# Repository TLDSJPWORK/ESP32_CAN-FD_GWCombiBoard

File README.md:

# ESP32 CAN-FD GateWay CombiBoard

ESP32開発ボード と MCP2518 + MCP2562FD CAN FD Busモジュール x2 を接続するための実験用基板、ESP32_CAN-FD_GWCombiBoardの資料です。

## 特徴

- [ESP32-DevKitC-32E](https://akizukidenshi.com/catalog/g/g115673/)、[ESP32-DevKitC-VE](https://akizukidenshi.com/catalog/g/g115674/)、[AE-ESP32-WROOM-32E-MINI](https://akizukidenshi.com/catalog/g/g116108/)に、[CAN FDモジュール](https://github.com/TLDSJPWORK/CAN-FD_Board)、[有機ELディスプレイ（SSD1306）](https://akizukidenshi.com/catalog/g/g112031/)、[三端子DC/DCレギュレーター](https://akizukidenshi.com/catalog/g/g111188/)をまとめて接続できる実験用基板です。モジュール間の配線の手間を減らし、通信実験の環境を組み立てやすくします。
- CAN FDモジュールを2個接続できるため、1台のESP32で2系統のCANバスを扱う構成を作れます。2つのバス間でメッセージを転送するゲートウェイの実験にも使えます。
- MCP2518向けのドライバ・ライブラリを使い、CANおよびCAN FDの送受信をプログラムできます。各チャンネルのGPIO割当は[仕様書](docs/hardware.md)にまとめています。
- 2系統のCAN信号と外部電源をDB9（D-Sub）コネクタにまとめられるため、実験装置への接続をケーブルで整理できます。
- [有機ELディスプレイ（SSD1306）](https://akizukidenshi.com/catalog/g/g112031/)用のMonitor端子を備え、通信状態や受信データを表示する構成に拡張できます。
- 三端子DC/DCレギュレーターを取り付けることで、12V電源から5Vへ降圧して給電する構成を作れます。
- KiCad設計データ・基板STEP・上下筐体STLを公開しているため、配線の確認や独自の改造、筐体の製作にも活用できます。

[双方向Gatewayサンプル](example/PassThroughGateway/README.md)を収録しています。通常CAN（500 kbit/s）とCAN FD（公称500 kbit/s、BRS時データ2 Mbit/s）の双方向転送を確認しています。試験条件と確認範囲はサンプルの説明を参照してください。

## 基板

DB9のみ実装した販売状態の実物写真です。その他の部品は未実装です。

| 表面 | 裏面 |
|---|---|
|  |  |

## 基板の設定

DB9は実装済みです。ESP32、CANモジュール、表示器、DC/DCなどは用途に応じて別途実装をお願い致します。

| 接続部 | 使い方 |
|---|---|
| J1・J2・J5 | ESP32開発ボードを接続します。3V3・5V・GNDと端子番号を合わせて取り付けます。 |
| J9・J10 | CAN FDモジュールの8ピン端子を接続します。モジュールの動作電圧ジャンパは3.3Vに設定して下さい |
| J3（Ch1）・J4（Ch2） | 各CANモジュールのCAN側端子を接続します。1番=CAN-H、2番=CAN-L、3番=GNDです。 |
| J6（Monitor） | SSD1306表示器用。1番=GND、2番=5V、3番=GPIO22、4番=GPIO21です。表示器側の端子順も確認してください。 |
| J7 | BP5293-50を接続します。1番=12V入力、2番=GND、3番=5V出力です。 |
| J8 | 外部電源入力。1番=12V、2番=GNDです。 |
| DB1（DB9・実装済み） | 販売時に実装済みです。2系統のCAN信号と外部電源をまとめて接続します。配列は[仕様書](docs/hardware.md)を参照してください。 |

CANの終端抵抗はCANモジュール側で設定し、各バスの両端で有効にします。外部電源とUSB給電は併用しない前提です。詳しい実装手順は[組立ガイド](docs/assembly.md)を参照してください。

## 対応部品・設計仕様

- 対応ESP32開発ボード：ESP32-DevKitC-32E／ESP32-DevKitC-VE／AE-ESP32-WROOM-32E-MINIのいずれか×1
- MCP2518 + MCP2562FD CAN FD Busモジュール（JP-WORKS-002）×1〜2
- 外部給電用DC/DC：BP5293-50（部品定格：入力7〜26V、出力5V・最大1A）
- 設計外形94×85mm、厚さ1.6mm
- DB9に2系統CANと外部電源を配置。端子配列は[仕様書](docs/hardware.md)を確認してください。

外部電源とUSB給電は併用しない前提です。部品定格は組立例全体の動作保証範囲ではありません。

## 内容物・別途必要な部品

販売内容物はDB9コネクタ実装済みの基板1枚です。その他の部品は別途購入し、はんだ付けして実装する構成です。
必要な部品と取付方法は[組立ガイド](docs/assembly.md)を参照してください。

## 使用例

ESP32開発ボードとCAN FDモジュール2枚を取り付け、DB9ケーブルを接続した組立例です。Monitor端子から表示器へ配線し、3Dプリントした上下筐体に収めています。本例ではUSB給電を前提としたため、筐体を一部切断し、USBをESP32に挿せるようにしております。

| モジュールを取り付けた状態 | 筐体に収めた状態 |
|---|---|
|  |  |

写真のESP32、CAN FDモジュール、表示器、ケーブル、筐体は販売品に含まれません。部品の向きは[組立ガイド](docs/assembly.md)、筐体データは[こちら](mechanical/README.md)を参照してください。

- [GateWay CombiBoardの組立と2バス通信の紹介（note）](https://note.com/tldsjpwork/n/n04cee544bb15)

## 資料

- [仕様・接続表](docs/hardware.md)
- [組立・動作確認ガイド](docs/assembly.md)
- [KiCad設計データ](hardware/kicad/)
- [製造データ](hardware/production/)
- [筐体・3Dデータ](mechanical/)
- [上下筐体のSTL・印刷ガイド（MakerWorld）](https://makerworld.com/ja/models/3444573-upper-and-lower-enclosure-for-esp32-can-fd-gateway)
- [ソフトウェアについて](example/README.md)
- [収録データとライセンス](docs/publication.md)

[回路図PDF](docs/schematic.pdf)も用意しております。基板の表裏写真、接続説明図、組立例を上記に掲載しています。

## 販売・問い合わせ

スイッチサイエンス様にて委託販売中
- [GateWay CombiBoardの販売ページ](https://www.switch-science.com/products/11498)
- 技術問い合わせ先：tldsjpwork@gmail.com

## ライセンス

本プロジェクトのオリジナル設計・製造データ・筐体データ・資料は[CC BY 4.0](LICENSE)で公開します。出典表示：JP WORKS / TLDSJPWORK、ESP32 CAN-FD GateWay CombiBoard。変更した場合は変更内容を明示してください。第三者の素材・ライブラリはそれぞれの利用条件に従います。

## 関連プロジェクト

- [CAN-FD_Board](https://github.com/TLDSJPWORK/CAN-FD_Board)：本基板に接続するCAN FD対応モジュールです。1チャンネルにつき1枚使用します。
- [ESP32_CAN-FD_CombiBoard](https://github.com/TLDSJPWORK/ESP32_CAN-FD_CombiBoard)：CANが1チャンネルでよい用途向けの接続基板です。用途に応じてこちらもご検討ください。

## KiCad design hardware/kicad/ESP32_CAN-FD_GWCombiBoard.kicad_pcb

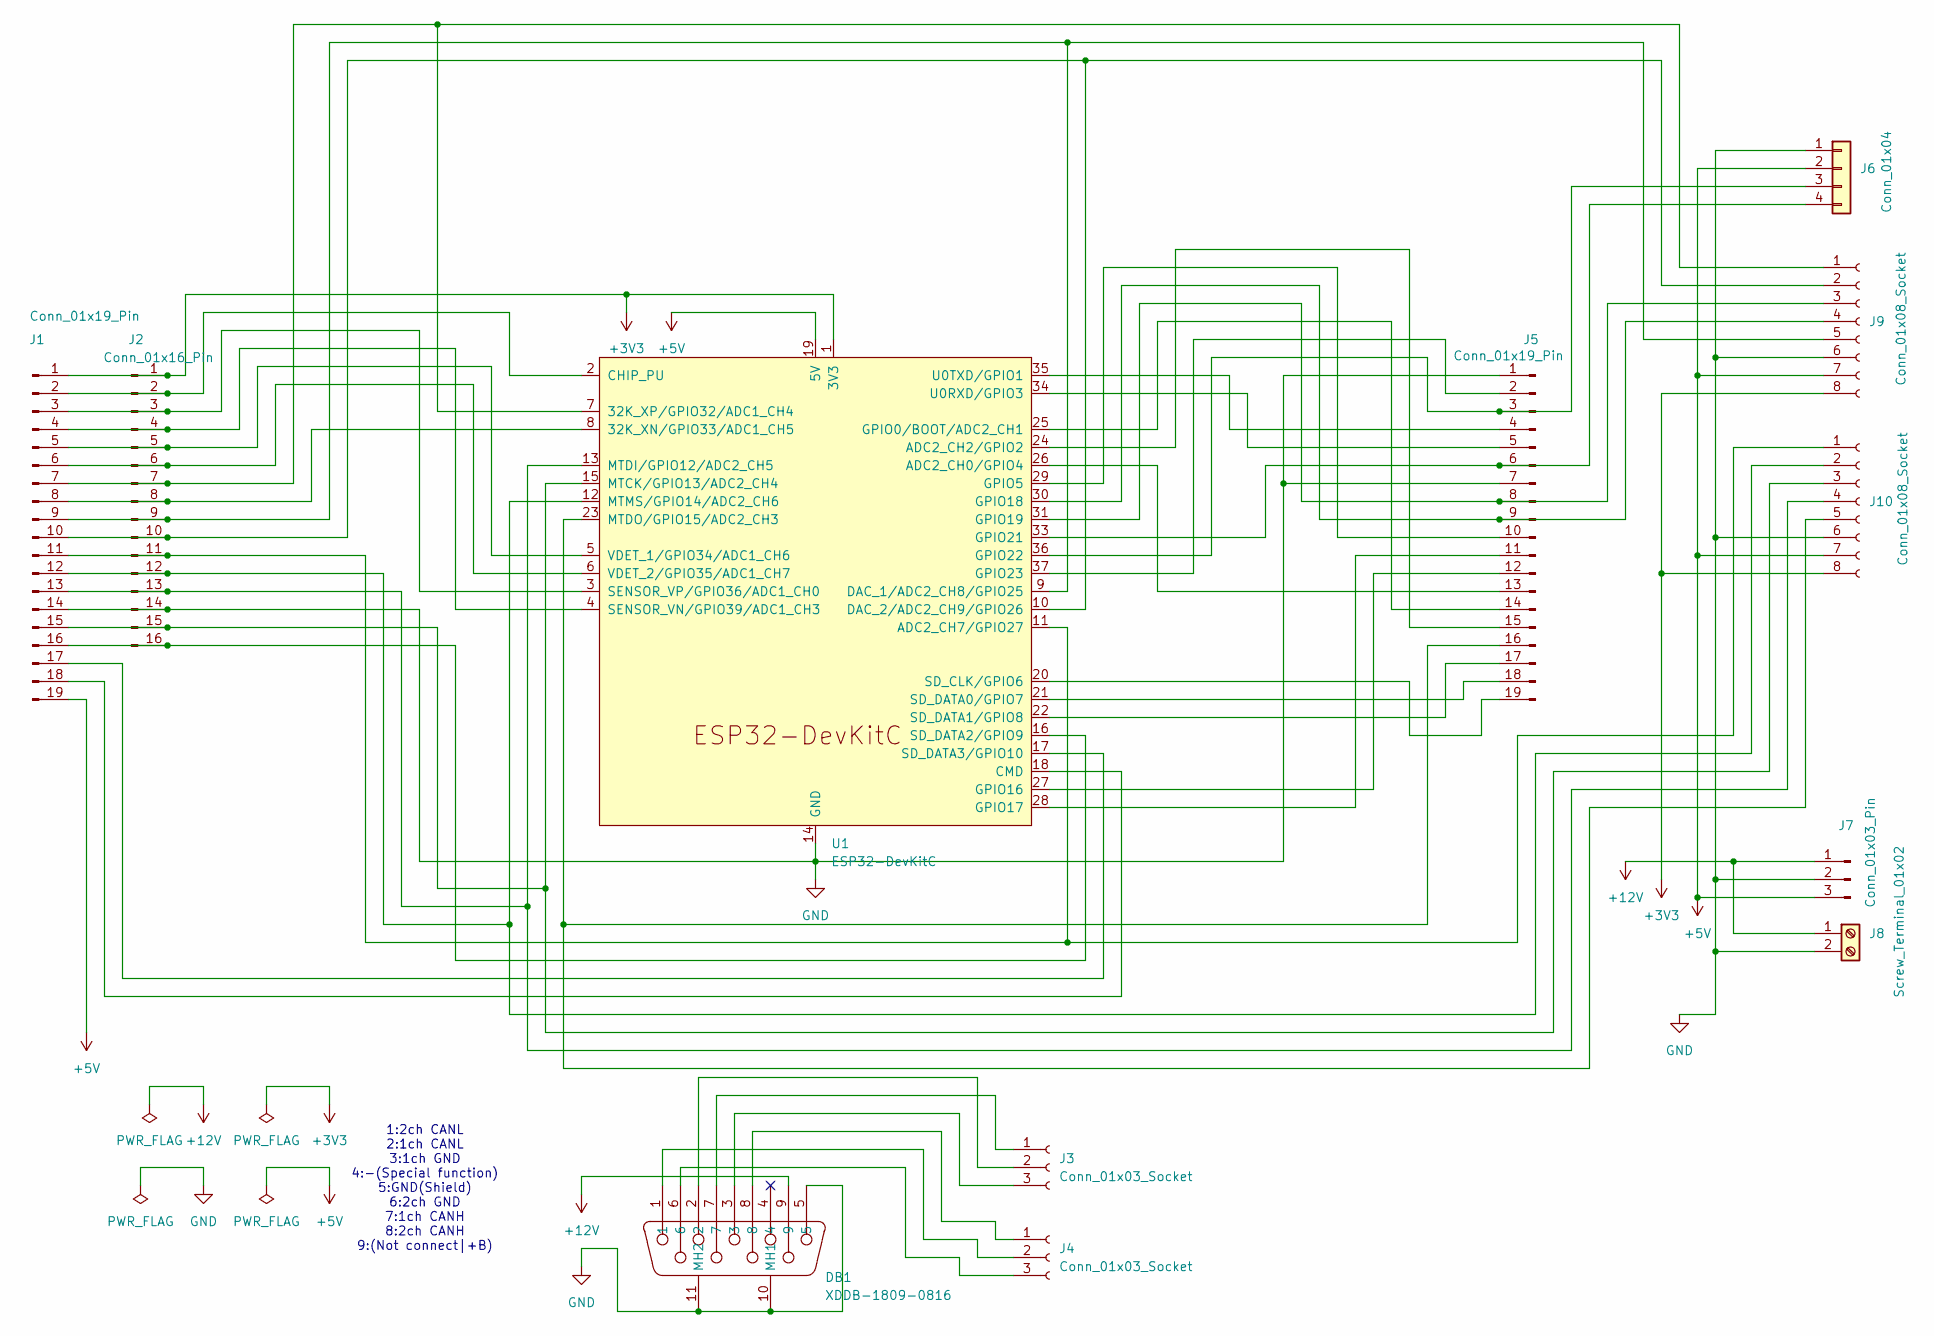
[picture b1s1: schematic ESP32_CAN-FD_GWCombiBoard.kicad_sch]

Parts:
DB1: XDDB-1809-0816; DB9-TH_LD09P33E4GV00LF; LCSC Part C7498157
J1, J5: Conn_01x19_Pin; PinSocket_1x19_P2.54mm_Vertical
J2: Conn_01x16_Pin; PinSocket_1x16_P2.54mm_Vertical
J3, J4: Conn_01x03_Socket; PinSocket_1x03_P2.54mm_Vertical
J6: Conn_01x04; JST_XH_B4B-XH-AM_1x04_P2.50mm_Vertical
J7: Conn_01x03_Pin; PinSocket_1x03_P2.54mm_Vertical
J8: Screw_Terminal_01x02; TerminalBlock_RND_205-00012_1x02_P5.00mm_Horizontal
J9, J10: Conn_01x08_Socket; PinSocket_1x08_P2.54mm_Vertical
U1: ESP32-DevKitC

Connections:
+3V3: J1.1, J2.1, J9.8, J10.8, U1.1 (3V3)
+5V: J1.19, J6.2, J7.3, J9.7, J10.7, U1.19 (5V)
+12V: DB1.9, J7.1, J8.1
GND: DB1.5, DB1.10 (MH1), DB1.11 (MH2), J1.14, J2.14, J5.1, J5.7, J6.1, J7.2, J8.2, J9.6, J10.6, U1.14 (GND), U1.32 (GND), U1.38 (GND)
unnamed: J1.2, J2.2, U1.2 (CHIP_PU)
unnamed: J1.3, J2.3, U1.3 (SENSOR_VP/GPIO36/ADC1_CH0)
unnamed: J1.4, J2.4, U1.4 (SENSOR_VN/GPIO39/ADC1_CH3)
unnamed: J1.5, J2.5, U1.5 (VDET_1/GPIO34/ADC1_CH6)
unnamed: J1.6, J2.6, U1.6 (VDET_2/GPIO35/ADC1_CH7)
unnamed: J1.7, J2.7, J9.1, U1.7 (32K_XP/GPIO32/ADC1_CH4)
unnamed: J1.8, J2.8, U1.8 (32K_XN/GPIO33/ADC1_CH5)
unnamed: J1.9, J2.9, J9.5, U1.9 (DAC_1/ADC2_CH8/GPIO25)
unnamed: J1.10, J2.10, J9.2, U1.10 (DAC_2/ADC2_CH9/GPIO26)
unnamed: J1.11, J2.11, J10.1, U1.11 (ADC2_CH7/GPIO27)
unnamed: J1.12, J2.12, J10.2, U1.12 (MTMS/GPIO14/ADC2_CH6)
unnamed: J1.13, J2.13, J10.4, U1.13 (MTDI/GPIO12/ADC2_CH5)
unnamed: J1.15, J2.15, J10.3, U1.15 (MTCK/GPIO13/ADC2_CH4)
unnamed: J1.16, J2.16, U1.16 (SD_DATA2/GPIO9)
unnamed: J1.17, U1.17 (SD_DATA3/GPIO10)
unnamed: J1.18, U1.18 (CMD)
unnamed: DB1.7, J3.1
unnamed: DB1.2, J3.2
unnamed: DB1.3, J3.3
unnamed: DB1.8, J4.1
unnamed: DB1.1, J4.2
unnamed: DB1.6, J4.3
unnamed: J5.2, U1.37 (GPIO23)
unnamed: J5.3, J6.3, U1.36 (GPIO22)
unnamed: J5.4, U1.35 (U0TXD/GPIO1)
unnamed: J5.5, U1.34 (U0RXD/GPIO3)
unnamed: J5.6, J6.4, U1.33 (GPIO21)
unnamed: J5.8, J9.3, U1.31 (GPIO19)
unnamed: J5.9, J9.4, U1.30 (GPIO18)
unnamed: J5.10, U1.29 (GPIO5)
unnamed: J5.11, U1.28 (GPIO17)
unnamed: J5.12, U1.27 (GPIO16)
unnamed: J5.13, U1.26 (ADC2_CH0/GPIO4)
unnamed: J5.14, U1.25 (GPIO0/BOOT/ADC2_CH1)
unnamed: J5.15, U1.24 (ADC2_CH2/GPIO2)
unnamed: J5.17, U1.22 (SD_DATA1/GPIO8)
unnamed: J5.18, U1.21 (SD_DATA0/GPIO7)
unnamed: J5.19, U1.20 (SD_CLK/GPIO6)
unnamed: J5.16, J10.5, U1.23 (MTDO/GPIO15/ADC2_CH3)

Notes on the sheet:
1:2ch CANL 2:1ch CANL 3:1ch GND 4:-(Special function) 5:GND(Shield) 6:2ch GND 7:1ch CANH 8:2ch CANH 9:(Not connect|+B)

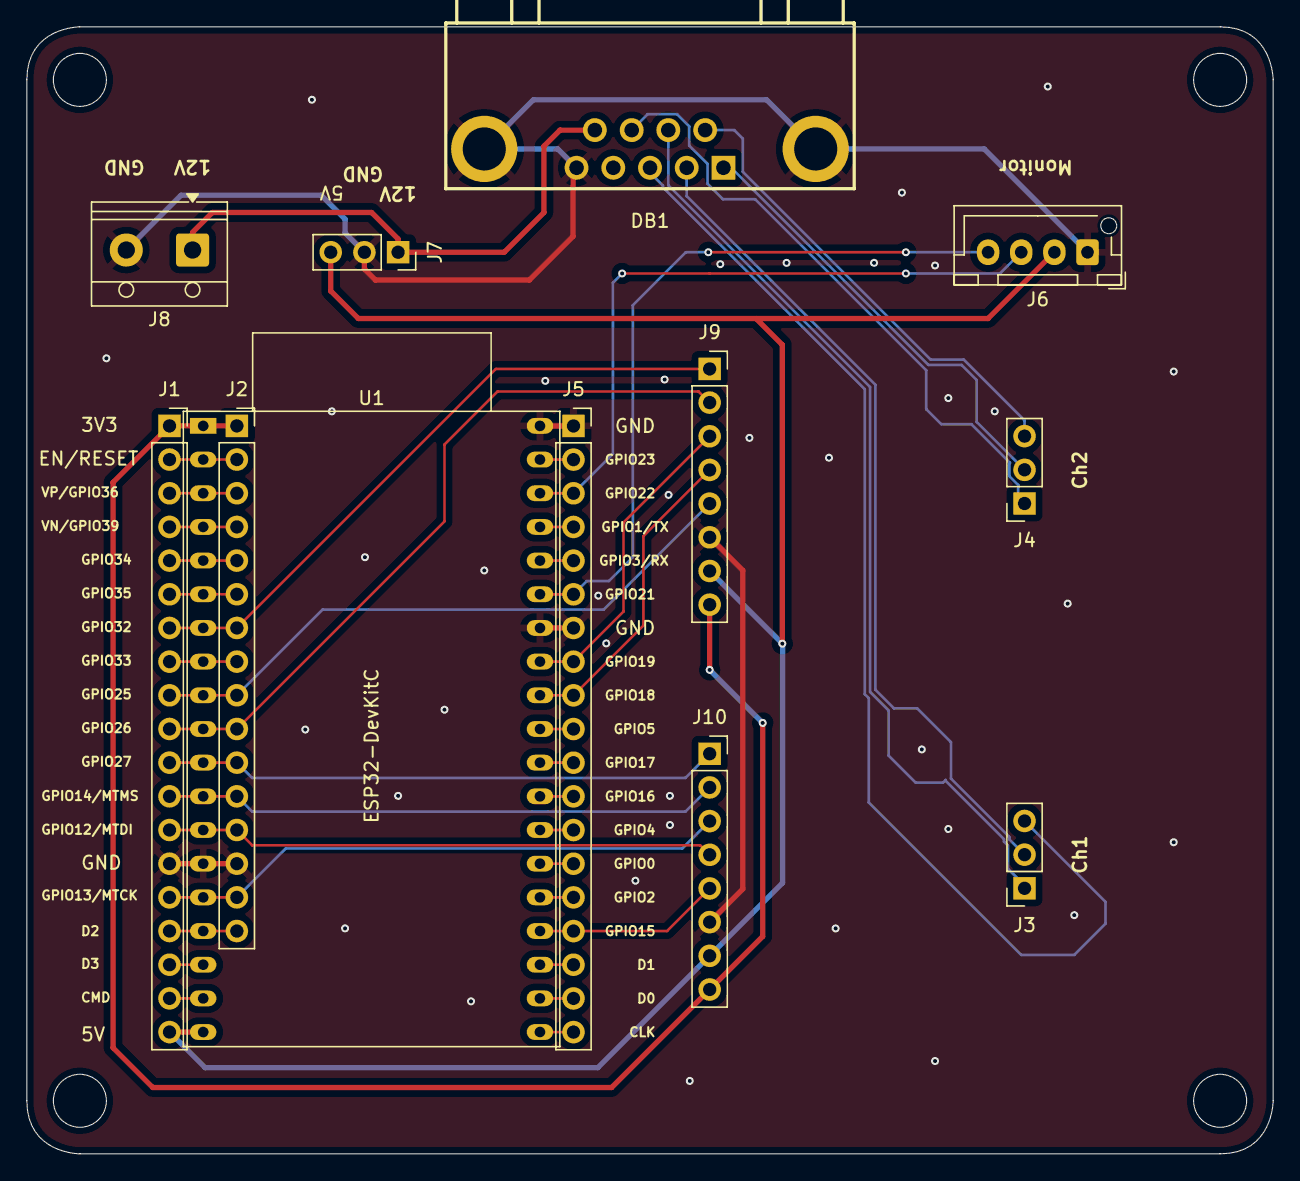
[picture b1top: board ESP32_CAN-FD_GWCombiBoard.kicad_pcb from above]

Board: 2 copper layers, 94.0 x 85.0 mm, 12 parts (0 on the bottom side), 43 nets.

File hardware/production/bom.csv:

Designator,Footprint,Quantity,Value,LCSC Part #
DB1,DB9-TH_LD09P33E4GV00LF,1,XDDB-1809-0816,C7498157
"J1, J5",PinSocket_1x19_P2.54mm_Vertical,2,Conn_01x19_Pin,
"J10, J9",PinSocket_1x08_P2.54mm_Vertical,2,Conn_01x08_Socket,
J2,PinSocket_1x16_P2.54mm_Vertical,1,Conn_01x16_Pin,
"J3, J4",PinSocket_1x03_P2.54mm_Vertical,2,Conn_01x03_Socket,
J6,JST_XH_B4B-XH-AM_1x04_P2.50mm_Vertical,1,Conn_01x04,
J7,PinSocket_1x03_P2.54mm_Vertical,1,Conn_01x03_Pin,
J8,TerminalBlock_RND_205-00012_1x02_P5.00mm_Horizontal,1,Screw_Terminal_01x02,
U1,,1,,
